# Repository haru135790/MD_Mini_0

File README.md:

# MD_Mini_0
人生初のMD設計。がばってたら許してね(to未来の自分)
バッテリーはLipo4sまたは6sを想定(他の電圧でも多分動く)

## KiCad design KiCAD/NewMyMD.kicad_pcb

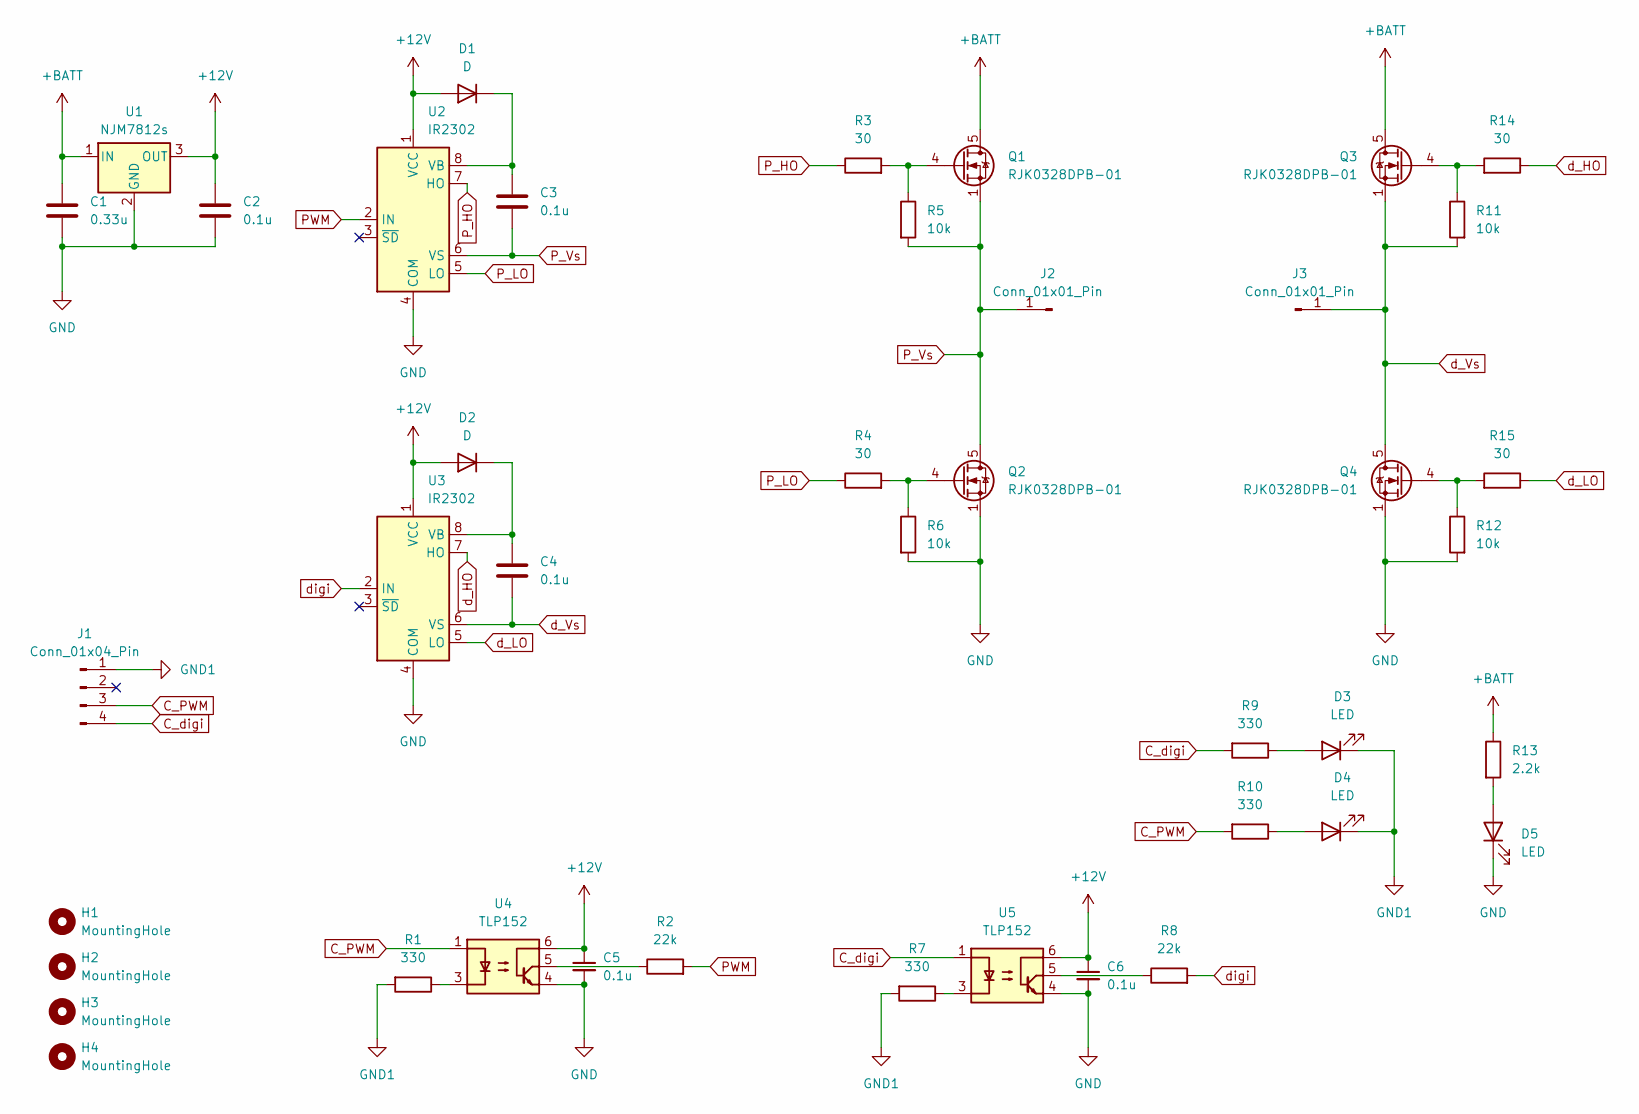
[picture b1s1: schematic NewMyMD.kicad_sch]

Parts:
C1: 0.33u; C_0603_1608Metric
C2, C3, C4, C5, C6: 0.1u; C_0603_1608Metric
D1, D2: D; D_0805_2012Metric
D3, D4, D5: LED; LED_0603_1608Metric
H1, H2, H3, H4: MountingHole; MountingHole_3.2mm_M3
J1: Conn_01x04_Pin; JST_XH_S4B-XH-A_1x04_P2.50mm_Horizontal
J2, J3: Conn_01x01_Pin
Q1, Q2, Q3, Q4: RJK0328DPB-01; LFPAK56
R1, R7, R9, R10: 330; R_0805_2012Metric
R2, R8: 22k; R_0603_1608Metric
R3, R4, R14, R15: 30; R_0603_1608Metric
R5, R6, R11, R12: 10k; R_0603_1608Metric
R13: 2.2k; R_0603_1608Metric
U1: NJM7812s; TO-252-2
U2, U3: IR2302; SO-8_3.9x4.9mm_P1.27mm
U4, U5: TLP152; MFSOP6-5_4.4x3.6mm_P1.27mm

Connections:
+12V: C2.1, C5.1, C6.1, D1.2 (A), D2.2 (A), U1.3 (OUT), U2.1 (VCC), U3.1 (VCC), U4.6, U5.6
+BATT: C1.1, Q1.5 (D), Q3.5 (D), R13.1, U1.1 (IN)
C_PWM: J1.3, R10.2, U4.1
C_digi: J1.4, R9.2, U5.1
GND: C1.2, C2.2, C5.2, C6.2, D5.1 (K), Q2.1 (S), Q2.2 (S), Q2.3 (S), Q4.1 (S), Q4.2 (S), Q4.3 (S), R6.2, R12.2, U1.2 (GND), U2.4 (COM), U3.4 (COM), U4.4, U5.4
GND1: D3.1 (K), D4.1 (K), J1.1, R1.2, R7.2
unnamed: C3.1, D1.1 (K), U2.8 (VB)
unnamed: C4.1, D2.1 (K), U3.8 (VB)
unnamed: D3.2 (A), R9.1
unnamed: D4.2 (A), R10.1
unnamed: D5.2 (A), R13.2
unnamed: Q1.4 (G), R3.2, R5.1
unnamed: Q2.4 (G), R4.2, R6.1
unnamed: Q3.4 (G), R11.1, R14.2
unnamed: Q4.4 (G), R12.1, R15.2
unnamed: R1.1, U4.3
unnamed: R2.1, U4.5
unnamed: R7.1, U5.3
unnamed: R8.1, U5.5
PWM: R2.2, U2.2 (IN)
P_HO: R3.1, U2.7 (HO)
P_LO: R4.1, U2.5 (LO)
P_Vs: C3.2, J2.1, Q1.1 (S), Q1.2 (S), Q1.3 (S), Q2.5 (D), R5.2, U2.6 (VS)
d_HO: R14.1, U3.7 (HO)
d_LO: R15.1, U3.5 (LO)
d_Vs: C4.2, J3.1, Q3.1 (S), Q3.2 (S), Q3.3 (S), Q4.5 (D), R11.2, U3.6 (VS)
digi: R8.2, U3.2 (IN)

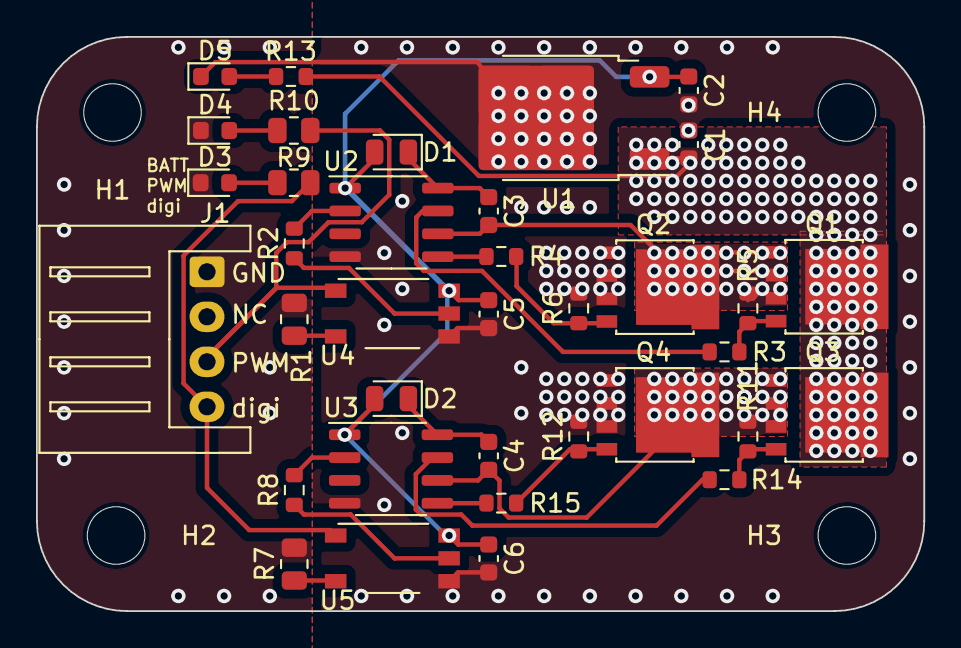
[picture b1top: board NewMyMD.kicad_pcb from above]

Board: 2 copper layers, 49.3 x 31.9 mm, 40 parts (0 on the bottom side), 27 nets.
